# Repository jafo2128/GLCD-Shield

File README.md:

# GLCD-Shield
The GLCD-Shield is a plug-on module with color display (128x128 pixel) and rotary encoder/navigation switch for Arduino/Genuino.

## Shop
* [GLCD-Shield with Rotary-Encoder](http://www.watterott.com/en/Arduino-GLCD-Shield)
* [GLCD-Shield with Joystick](http://www.watterott.com/en/Arduino-GLCD-Shield-Joystick)

## Features
* Color display with 128x128 pixel
* Rotary-Encoder or Joystick / Navigation-Switch
* Controller: NXP LPC1114 ARM Cortex-M0 with Open-Source Firmware
* Interface: UART, I2C, SPI/SSI (Mode 3, up to 4MHz)
* Backlight dimmable via interface
* 3.3V - 5V tolerant IOs

## Hardware
* 
* [Schematics + Layout](https://github.com/watterott/GLCD-Shield/tree/master/hardware)

## Software
* [General Arduino Examples](https://github.com/watterott/MI0283QT-Adapter/tree/master/firmware/examples)
* [Arduino Library and Examples](https://github.com/watterott/Arduino-Libs)
* [Firmware Source Code](https://github.com/watterott/MI0283QT-Adapter/tree/master/firmware)
* [Firmware Update Guide](https://github.com/watterott/MI0283QT-Adapter/blob/master/firmware/update_guide/README.md)
* [Command Description](https://github.com/watterott/MI0283QT-Adapter/blob/master/firmware/docu/README.md)

Finally words from us Archivers and Developers.. 

##### Donate

People from time to time wish to donate a little money. Donating won't get you anything special, other than a warm feeling inside, and possibly urge me to produce more freely available material for interesting projects. You can donate via [PayPal](https://www.paypal.com), just click [donate](https://www.paypal.com/cgi-bin/webscr?cmd=_s-xclick&hosted_button_id=3PXVSLXFBS45E) button available below - it will redirect you to the secured PayPal page where you can provide donation amount (there is no minimal value). Any donations are apreciated greatly, and we thank you all in advance for your support along the ways..

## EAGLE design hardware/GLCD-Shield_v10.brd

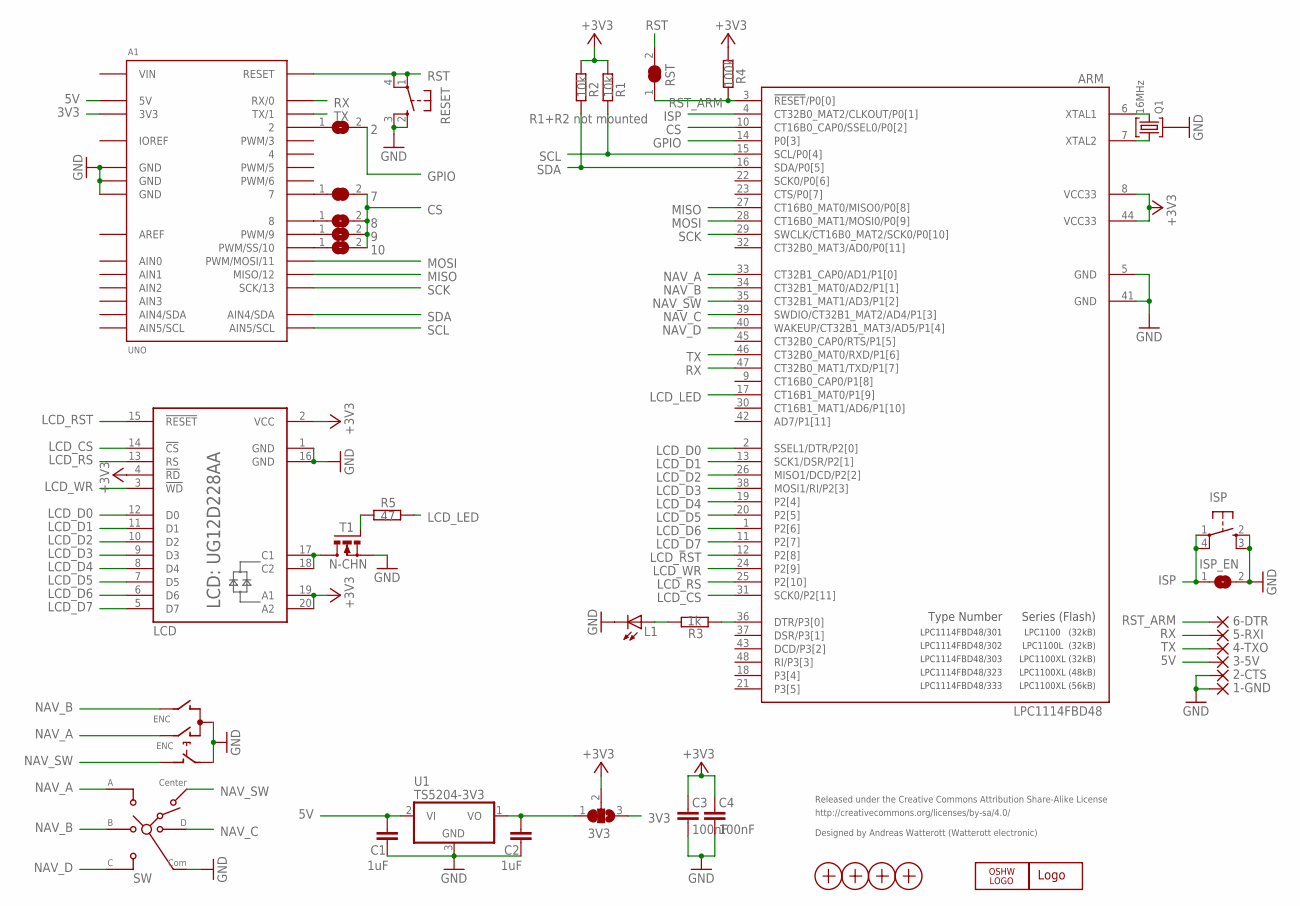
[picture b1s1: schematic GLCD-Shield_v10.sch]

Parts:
1-GND, 2-CTS, 3-5V, 4-TXO, 5-RXI, 6-DTR: WIREPADSMD1,27-254; SMD1,27-2,54
2, 7, 8, 9, 10: SJ
3V3: SJ2W; SJ_2
A1: UNO
ARM: LPC1114FBD48; LQFP48
C1, C2: 1uF; C0603
C3, C4: 100nF; C0603
ENC: EC12E_SW; ALPS_EC12E_SW
ISP: SW_SMDS; SW_SMD4@1
ISP_EN: SJ
L1: LEDCHIPLED_0603; CHIPLED_0603
LCD: UG12D228AA
LOGO1: OSHW_LOGO_6MILX0100-NT; OSHW_6X100_NOTEXT
Q1: 16MHz; SMD_OSC_35X15
R1, R2: 10k; R0603
R3: 1k; R0603
R4: 100k; R0603
R5: 47; R0603
RESET: SW_SMDS; SW_SMD4@1
RST: SJ
SW: SKQUCAA010; SKQU
T1: N-CHN; MICRO3
U1: TS5204-3V3; SOT23
U$1: WE-LOGOPLACE; WE-LOGO
X1, X2, X3, X4: PASSER

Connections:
2X: 2.1, A1.2
3V3: 3V3.3, A1.3V3
3V_OUT: 3V3.1, C2.1, U1.1 (VO)
5V: 3-5V.1, A1.5V, C1.1, U1.2 (VI)
7: 7.1, A1.7
8: 8.1, A1.8
9: 9.1, A1.9 (PWM/9)
10: 10.1, A1.10 (PWM/SS/10)
+3V3: 3V3.2, ARM.8 (VCC33), ARM.44 (VCC33), C3.1, C4.1, LCD.2 (VCC), LCD.4 (!RD), LCD.19 (A1), LCD.20 (A2), R1.2, R2.2, R4.2
AREF: A1.AREF
C: LCD.17 (C1), LCD.18 (C2), T1.3 (D)
CS: 7.2, 8.2, 9.2, 10.2, ARM.10 (CT16B0_CAP0/SSEL0/P0[2])
GND: 1-GND.1, 2-CTS.1, A1.GND@1 (GND), A1.GND@2 (GND), A1.GND@3 (GND), ARM.5 (GND), ARM.41 (GND), C1.2, C2.2, C3.2, C4.2, ENC.C, ENC.E (2), ISP.2 (S), ISP.3 (S1), ISP_EN.2, L1.C, LCD.1 (GND), LCD.16 (GND), Q1.GND, RESET.2 (S), RESET.3 (S1), SW.COMMON, T1.2 (S), U1.3 (GND)
GPIO: 2.2, ARM.14 (P0[3])
IOREF: A1.IOREF
ISP: ARM.4 (CT32B0_MAT2/CLKOUT/P0[1]), ISP.1, ISP.4 (P1), ISP_EN.1
LCD_CS: ARM.31 (SCK0/P2[11]), LCD.14 (!CS)
LCD_D0: ARM.2 (SSEL1/DTR/P2[0]), LCD.12 (D0)
LCD_D1: ARM.13 (SCK1/DSR/P2[1]), LCD.11 (D1)
LCD_D2: ARM.26 (MISO1/DCD/P2[2]), LCD.10 (D2)
LCD_D3: ARM.38 (MOSI1/RI/P2[3]), LCD.9 (D3)
LCD_D4: ARM.19 (P2[4]), LCD.8 (D4)
LCD_D5: ARM.20 (P2[5]), LCD.7 (D5)
LCD_D6: ARM.1 (P2[6]), LCD.6 (D6)
LCD_D7: ARM.11 (P2[7]), LCD.5 (D7)
LCD_LED: ARM.17 (CT16B1_MAT0/P1[9]), R5.2
LCD_RS: ARM.25 (P2[10]), LCD.13 (RS)
LCD_RST: ARM.12 (P2[8]), LCD.15 (!RESET)
LCD_WR: ARM.24 (P2[9]), LCD.3 (!WD)
LED: ARM.36 (DTR/P3[0]), R3.1
LEDPWM: R5.1, T1.1 (G)
MISO: A1.12 (MISO/12), ARM.27 (CT16B0_MAT0/MISO0/P0[8])
MOSI: A1.11 (PWM/MOSI/11), ARM.28 (CT16B0_MAT1/MOSI0/P0[9])
unnamed: ARM.6 (XTAL1), Q1.2
unnamed: ARM.7 (XTAL2), Q1.1
unnamed: L1.A, R3.2
NAV_A: ARM.33 (CT32B1_CAP0/AD1/P1[0]), ENC.A, SW.A
NAV_B: ARM.34 (CT32B1_MAT0/AD2/P1[1]), ENC.B, SW.B
NAV_C: ARM.39 (SWDIO/CT32B1_MAT2/AD4/P1[3]), SW.D
NAV_D: ARM.40 (WAKEUP/CT32B1_MAT3/AD5/P1[4]), SW.C
NAV_SW: ARM.35 (CT32B1_MAT1/AD3/P1[2]), ENC.D (1), SW.CENTER
RST: A1.RST (RESET), RESET.1, RESET.4 (P1), RST.2
RST_ARM: 6-DTR.1, ARM.3 (!RESET!/P0[0]), R4.1, RST.1
RX: 5-RXI.1, A1.0 (RX/0), ARM.47 (CT32B0_MAT1/TXD/P1[7])
SCK: A1.13 (SCK/13), ARM.29 (SWCLK/CT16B0_MAT2/SCK0/P0[10])
SCL: A1.SCL (AIN5/SCL), ARM.15 (SCL/P0[4]), R1.1
SDA: A1.SDA (AIN4/SDA), ARM.16 (SDA/P0[5]), R2.1
TX: 4-TXO.1, A1.1 (TX/1), ARM.46 (CT32B0_MAT0/RXD/P1[6])
VIN: A1.VIN

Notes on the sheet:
Released under the Creative Commons Attribution Share-Alike License
http://creativecommons.org/licenses/by-sa/4.0/
Designed by Andreas Watterott (Watterott electronic)
R1+R2 not mounted
LPC1100 (32kB)
LPC1100L (32kB)
LPC1100XL (32kB)
LPC1100XL (48kB)
LPC1100XL (56kB)
Type Number
Series (Flash)
LPC1114FBD48/301
LPC1114FBD48/302
LPC1114FBD48/303
LPC1114FBD48/323
LPC1114FBD48/333

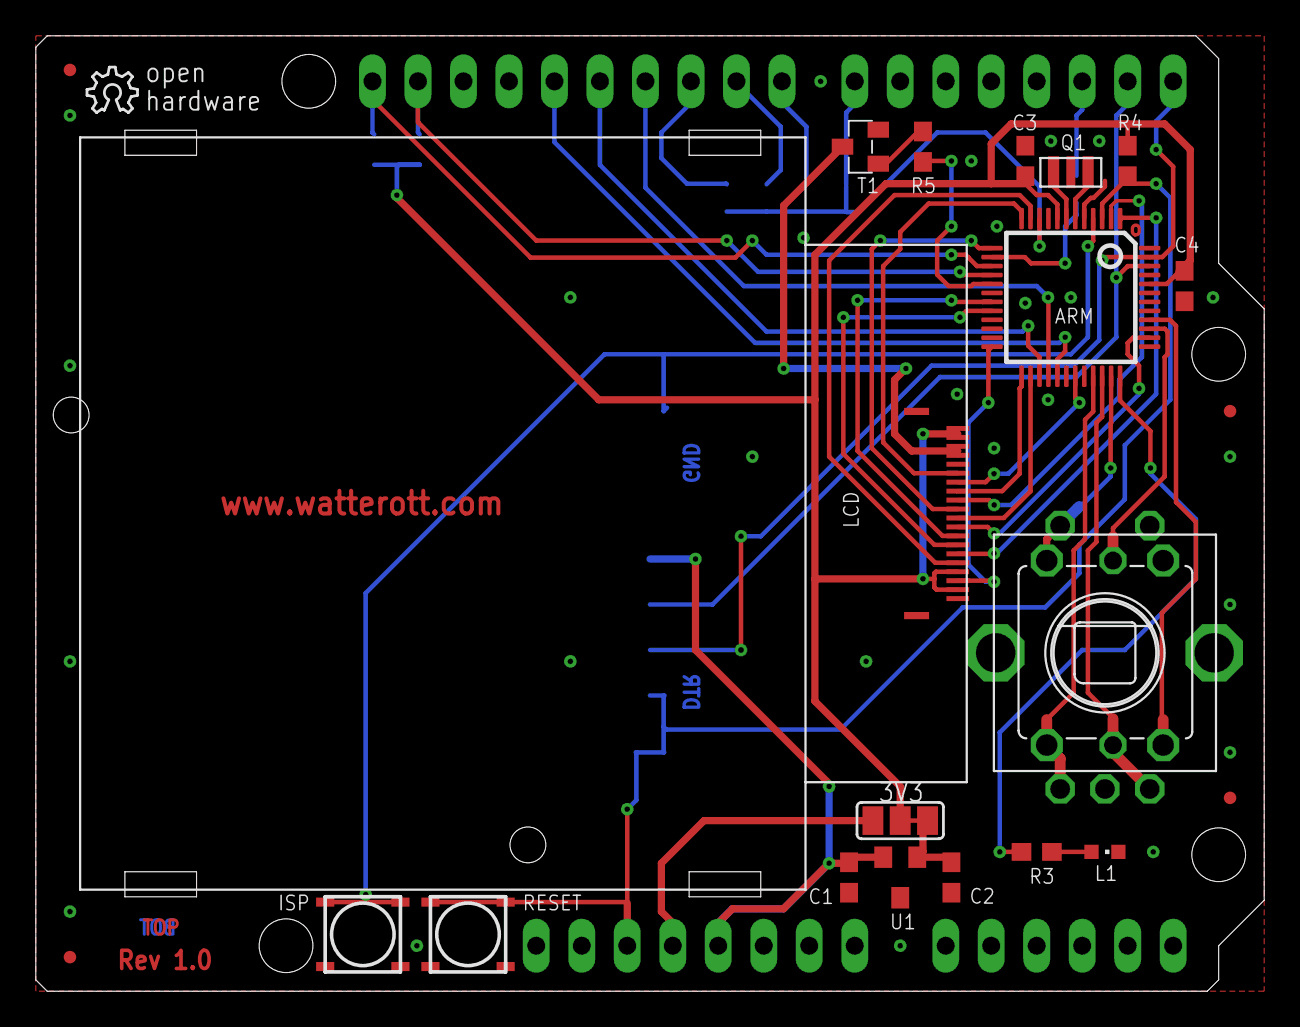
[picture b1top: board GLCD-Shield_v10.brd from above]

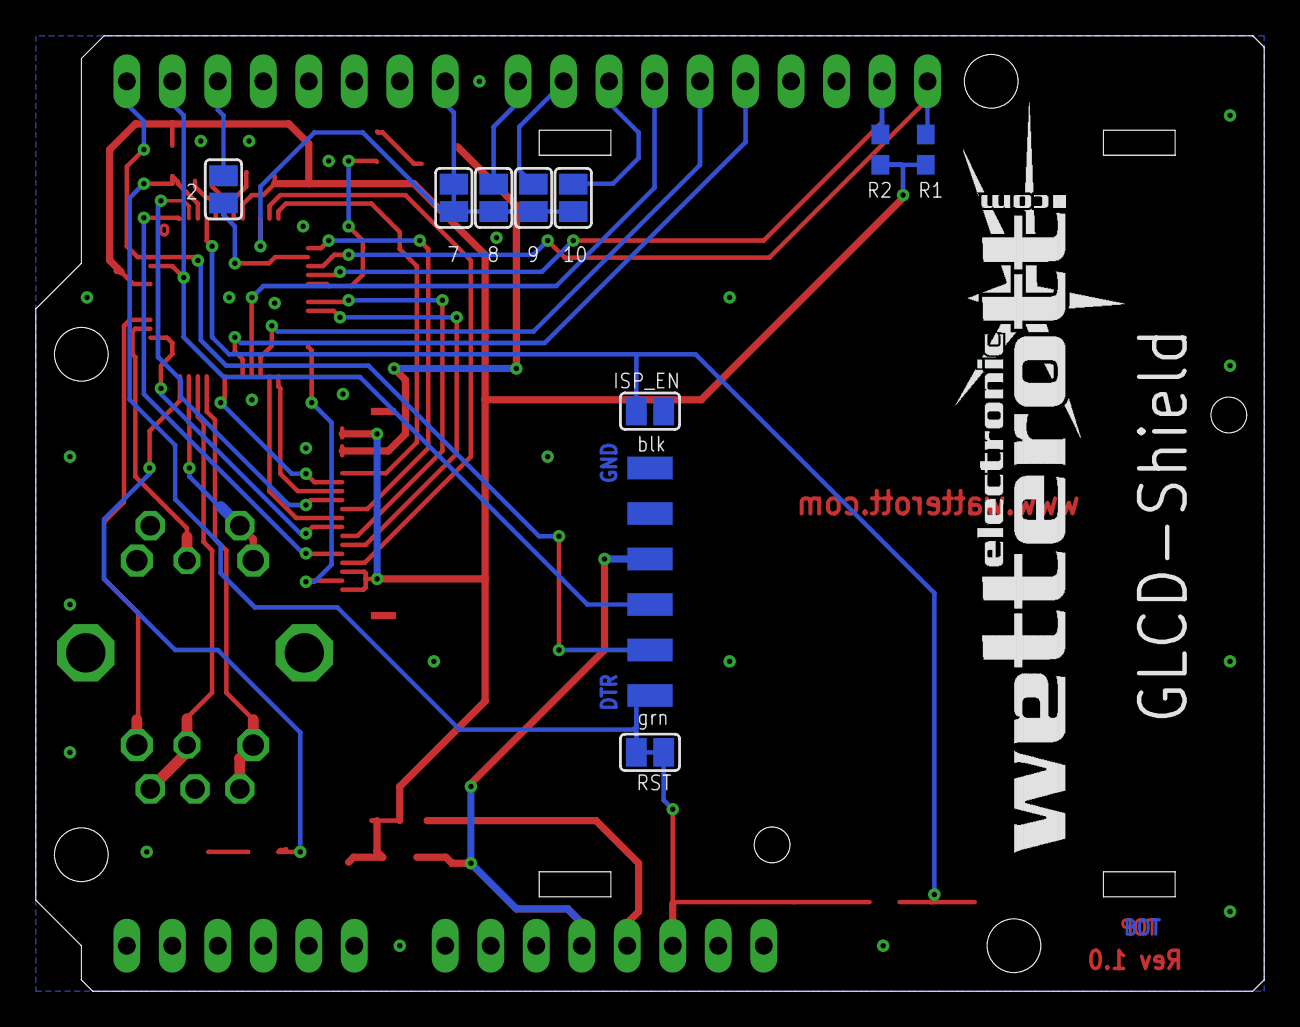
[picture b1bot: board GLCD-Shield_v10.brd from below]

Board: 2 copper layers, 68.6 x 53.3 mm, 40 parts (16 on the bottom side), 46 nets.

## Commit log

2013-05-27 added schematic and image
2013-06-17 updated schematics
2013-07-04 updated image
2013-09-21 added hardware diagram
2014-03-10 updated license infos
2014-08-15 updated schematic and layout files
2014-08-21 updated layout and schematics
2014-11-06 cleaned up schematics and layout
2015-01-10 moved image
2015-08-21 changed path structure
